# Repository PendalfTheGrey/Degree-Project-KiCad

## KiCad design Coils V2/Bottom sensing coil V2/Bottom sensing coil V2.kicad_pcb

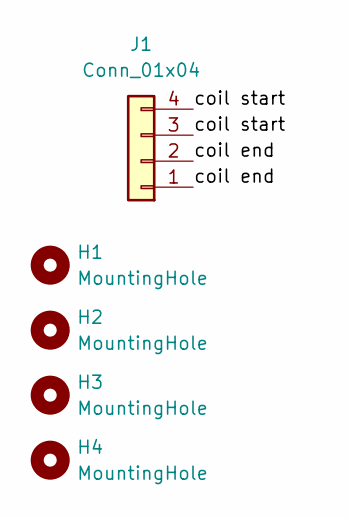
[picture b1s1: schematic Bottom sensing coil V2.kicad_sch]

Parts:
H1, H2, H3, H4: MountingHole; MountingHole_3.2mm_M3_Pad
J1: Conn_01x04; PinHeader_1x04_P2.54mm_Horizontal

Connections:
/coil end: J1.1, J1.2
/coil start: J1.3, J1.4

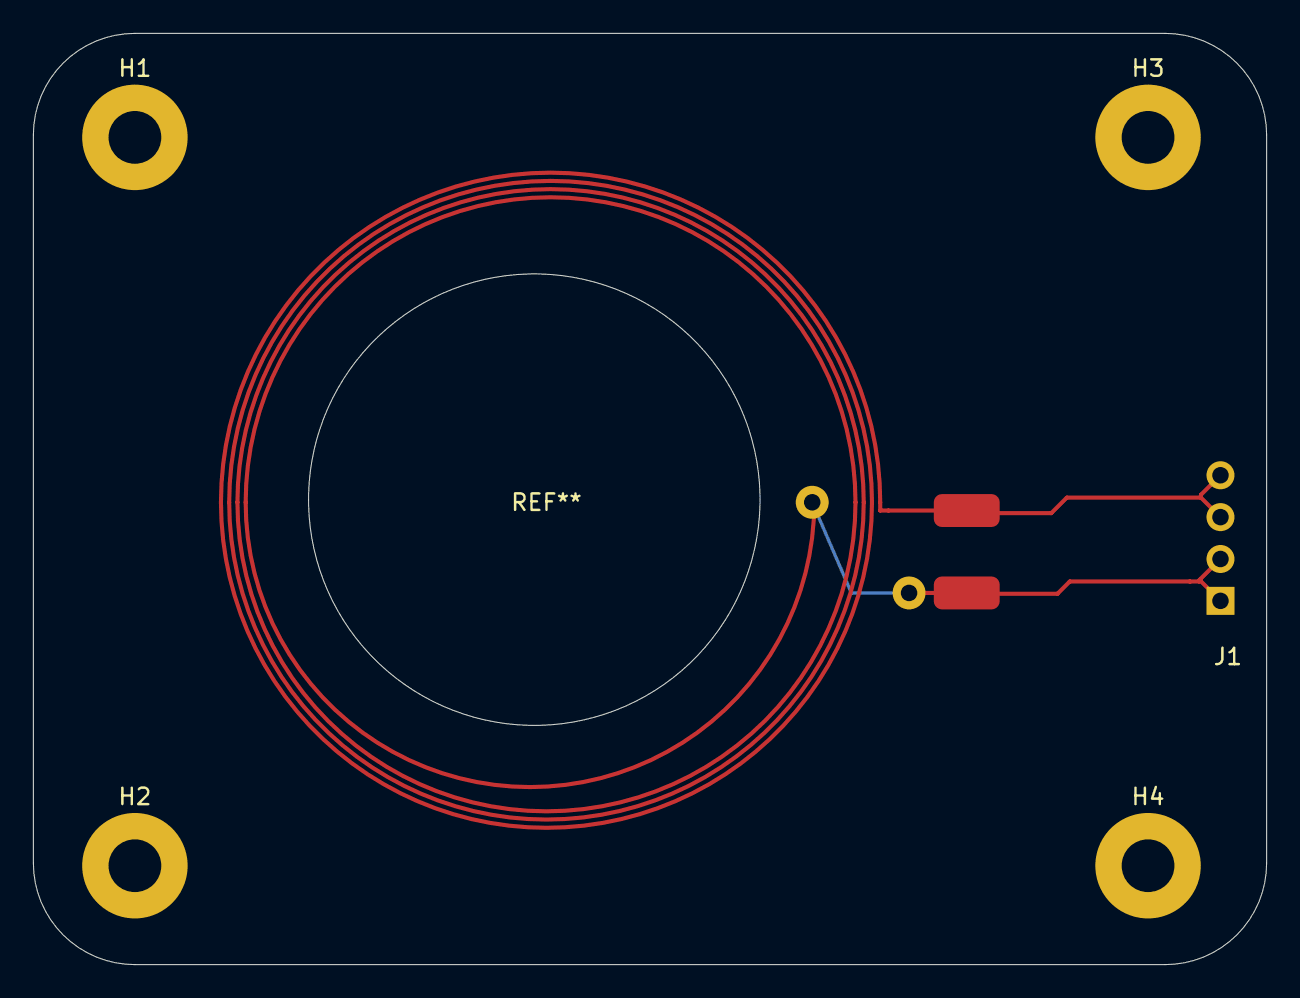
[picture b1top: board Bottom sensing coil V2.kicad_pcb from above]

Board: 2 copper layers, 74.8 x 56.5 mm, 5 parts (1 on the bottom side), 2 nets.

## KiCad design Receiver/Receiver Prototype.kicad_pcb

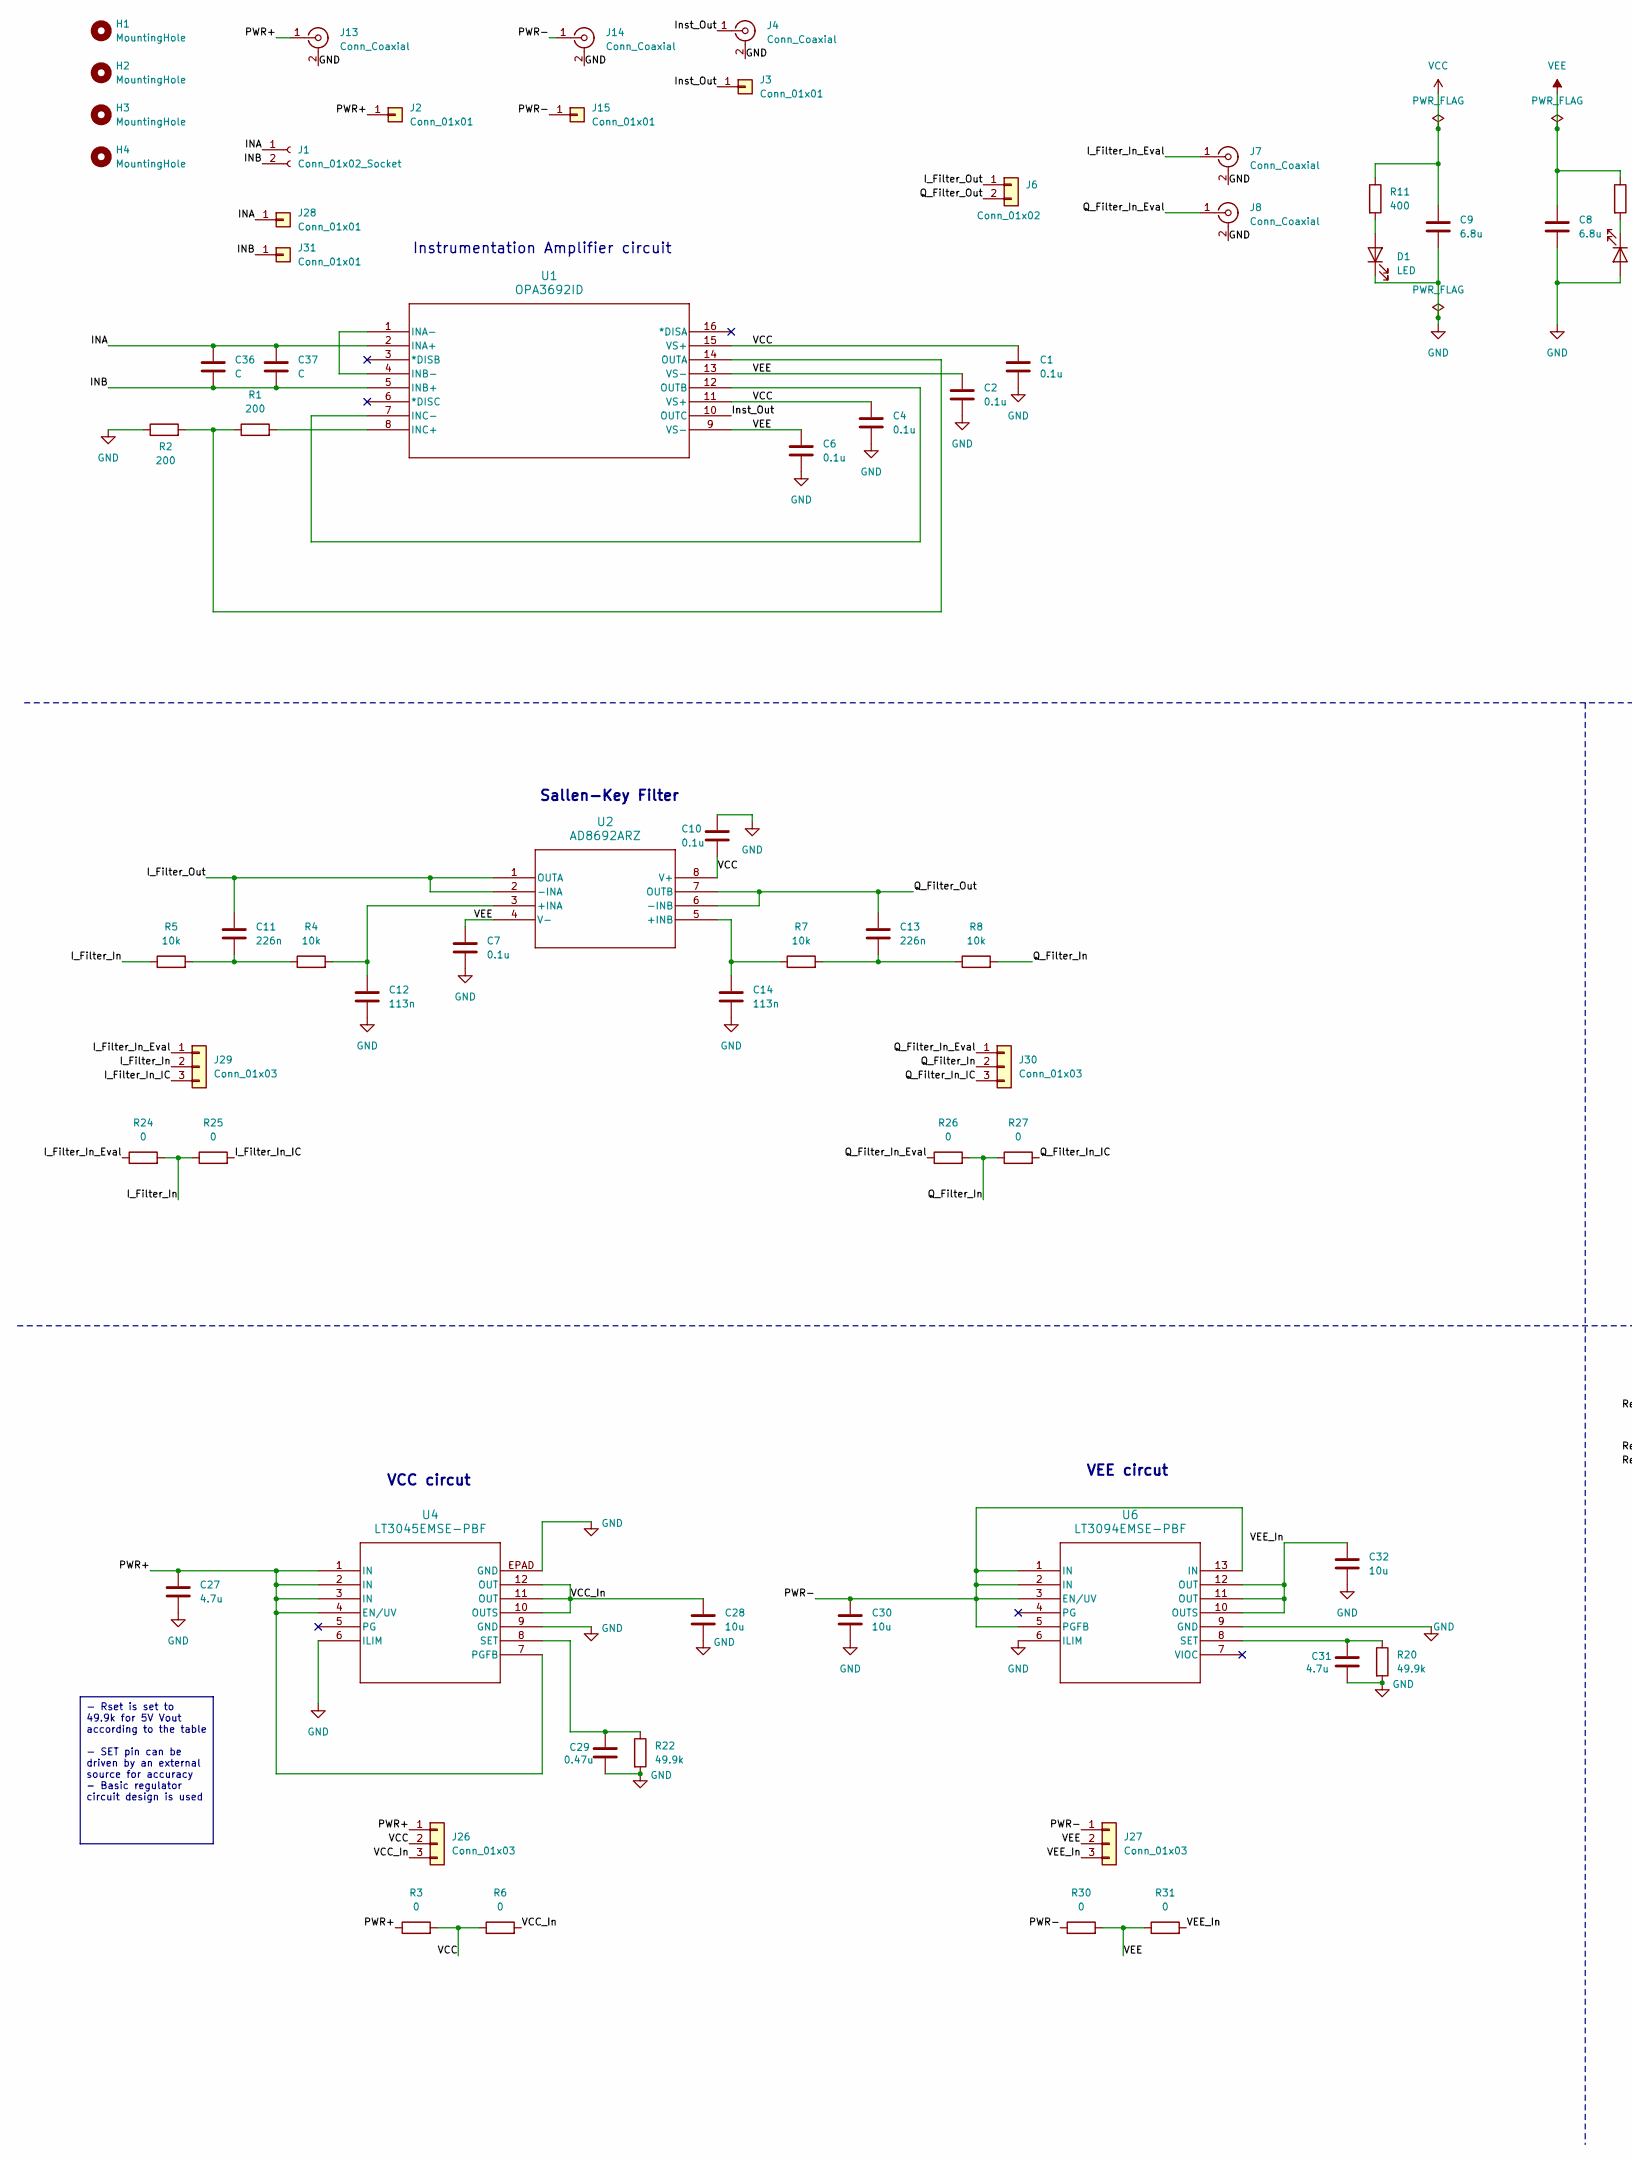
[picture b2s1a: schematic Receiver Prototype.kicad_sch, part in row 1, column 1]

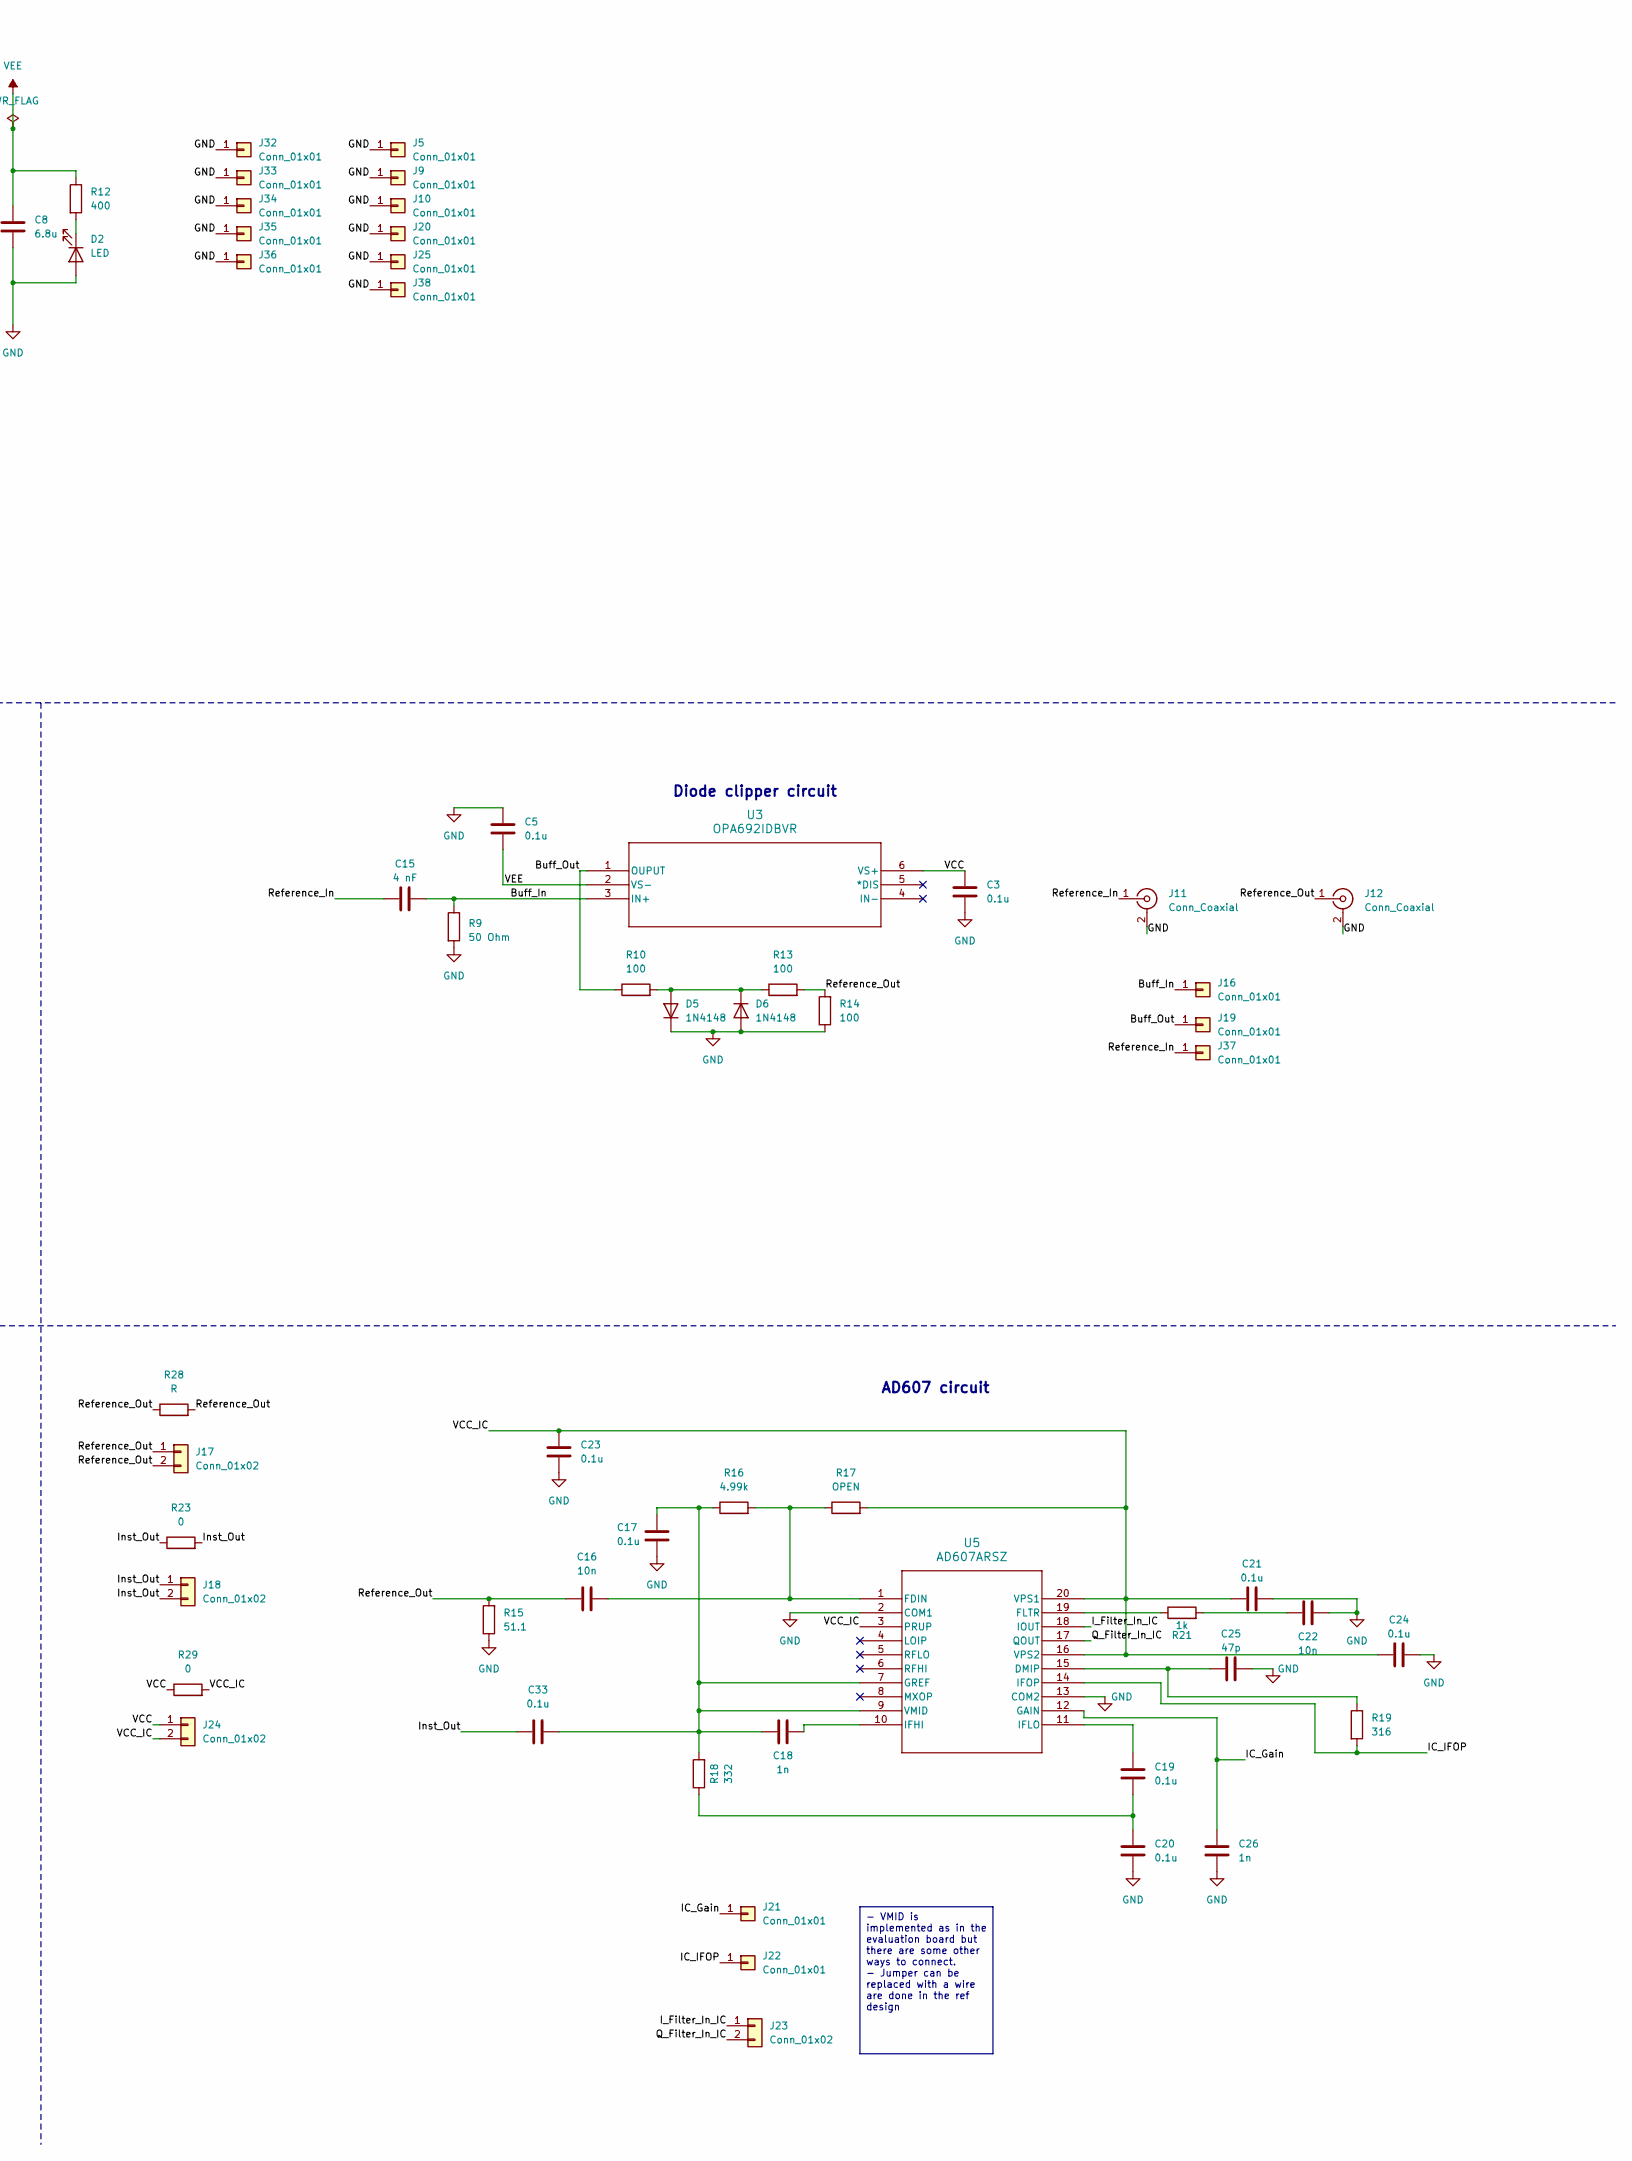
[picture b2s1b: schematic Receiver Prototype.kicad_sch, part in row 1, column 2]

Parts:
C1, C2, C3, C4, C5, C6, C7, C10, C17, C19, C20, C21, C23, C24, C33: 0.1u; C_0603_1608Metric_Pad1.08x0.95mm_HandSolder
C8, C9: 6.8u; C_0603_1608Metric_Pad1.08x0.95mm_HandSolder
C11, C13: 226n; C_0603_1608Metric_Pad1.08x0.95mm_HandSolder
C12, C14: 113n; C_0603_1608Metric_Pad1.08x0.95mm_HandSolder
C15: 4 nF; C_0603_1608Metric_Pad1.08x0.95mm_HandSolder
C16, C22: 10n; C_0603_1608Metric_Pad1.08x0.95mm_HandSolder
C18, C26: 1n; C_0603_1608Metric_Pad1.08x0.95mm_HandSolder
C25: 47p; C_0603_1608Metric_Pad1.08x0.95mm_HandSolder
C27, C31: 4.7u; C_0603_1608Metric_Pad1.08x0.95mm_HandSolder
C28, C30, C32: 10u; C_0603_1608Metric_Pad1.08x0.95mm_HandSolder
C29: 0.47u; C_0603_1608Metric_Pad1.08x0.95mm_HandSolder
C36, C37: C; C_0603_1608Metric_Pad1.08x0.95mm_HandSolder
D1, D2: LED; LED_0603_1608Metric_Pad1.05x0.95mm_HandSolder
D5, D6: 1N4148; D_0805_2012Metric_Pad1.15x1.40mm_HandSolder
H1, H2, H3, H4: MountingHole; MountingHole_3.2mm_M3_Pad
J1: Conn_01x02_Socket; PinSocket_1x02_P2.54mm_Horizontal
J2, J3, J5, J9, J10, J15, J16, J19, J20, J21, J22, J25, J28, J31, J32, J33, J34, J35, J36, J37, J38: Conn_01x01; PinHeader_1x01_P2.54mm_Vertical
J4, J7, J8, J11, J12: Conn_Coaxial; SMA_Amphenol_132289_EdgeMount
J6, J17, J18, J23, J24: Conn_01x02; PinHeader_1x02_P2.54mm_Vertical
J13, J14: Conn_Coaxial; BNC_Amphenol_112640_Edge_mount
J26, J27, J29, J30: Conn_01x03; PinHeader_1x03_P2.54mm_Vertical
R1, R2: 200; R_0603_1608Metric_Pad0.98x0.95mm_HandSolder
R3, R6, R23, R24, R25, R26, R27, R29, R30, R31: 0; R_0603_1608Metric_Pad0.98x0.95mm_HandSolder
R4, R5, R7, R8: 10k; R_0603_1608Metric_Pad0.98x0.95mm_HandSolder
R9: 50 Ohm; R_0603_1608Metric_Pad0.98x0.95mm_HandSolder
R10, R13, R14: 100; R_0603_1608Metric_Pad0.98x0.95mm_HandSolder
R11, R12: 400; R_0603_1608Metric_Pad0.98x0.95mm_HandSolder
R15: 51.1; R_0603_1608Metric_Pad0.98x0.95mm_HandSolder
R16: 4.99k; R_0603_1608Metric_Pad0.98x0.95mm_HandSolder
R17: OPEN; R_0603_1608Metric_Pad0.98x0.95mm_HandSolder
R18: 332; R_0603_1608Metric_Pad0.98x0.95mm_HandSolder
R19: 316; R_0603_1608Metric_Pad0.98x0.95mm_HandSolder
R20, R22: 49.9k; R_0603_1608Metric_Pad0.98x0.95mm_HandSolder
R21: 1k; R_0603_1608Metric_Pad0.98x0.95mm_HandSolder
R28: R; R_0603_1608Metric_Pad0.98x0.95mm_HandSolder
U1: OPA3692ID; DBQ16
U2: AD8692ARZ; SOIC127P600X175-8N
U3: OPA692IDBVR; DBV6
U4: LT3045EMSE-PBF; MSOP12_MSE_ADI
U5: AD607ARSZ; RS_20_ADI
U6: LT3094EMSE-PBF; 05-08-1666_ADI

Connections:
/Buff_In: C15.2, J16.1, R9.1, U3.3 (IN+)
/Buff_Out: J19.1, R10.1, U3.1 (OUPUT)
/IC_Gain: C26.1, J21.1, U5.12 (GAIN)
/IC_IFOP: J22.1, R19.2, U5.14 (IFOP)
/INA: C36.1, C37.1, J1.1, J28.1, U1.2 (INA+)
/INB: C36.2, C37.2, J1.2, J31.1, U1.5 (INB+)
/I_Filter_In: J29.2, R5.1, R24.2, R25.1
/I_Filter_In_Eval: J7.1 (In), J29.1, R24.1
/I_Filter_In_IC: J23.1, J29.3, R25.2, U5.18 (IOUT)
/I_Filter_Out: C11.1, J6.1, U2.1 (OUTA), U2.2 (-INA)
/Inst_Out: C33.1, J3.1, J4.1 (In), J18.1, J18.2, R23.1, R23.2, U1.10 (OUTC)
/PWR+: C27.1, J2.1, J13.1 (In), J26.1, R3.1, U4.1 (IN), U4.2 (IN), U4.3 (IN), U4.4 (EN/UV), U4.7 (PGFB)
/PWR-: C30.1, J14.1 (In), J15.1, J27.1, R30.1, U6.1 (IN), U6.2 (IN), U6.3 (EN/UV), U6.5 (PGFB), U6.13 (IN)
/Q_Filter_In: J30.2, R8.2, R26.2, R27.1
/Q_Filter_In_Eval: J8.1 (In), J30.1, R26.1
/Q_Filter_In_IC: J23.2, J30.3, R27.2, U5.17 (QOUT)
/Q_Filter_Out: C13.1, J6.2, U2.6 (-INB), U2.7 (OUTB)
/Reference_In: C15.1, J11.1 (In), J37.1
/Reference_Out: C16.1, J12.1 (In), J17.1, J17.2, R13.2, R14.2, R15.2, R28.1, R28.2
/VCC_IC: C21.1, C23.2, C24.1, J24.2, R17.2, R29.2, U5.3 (PRUP), U5.16 (VPS2), U5.20 (VPS1)
/VCC_In: C28.1, J26.3, R6.2, U4.10 (OUTS), U4.11 (OUT), U4.12 (OUT)
/VEE_In: C32.1, J27.3, R31.2, U6.10 (OUTS), U6.11 (OUT), U6.12 (OUT)
GND: C1.2, C2.2, C3.2, C4.2, C5.1, C6.2, C7.2, C8.2, C9.2, C10.1, C12.2, C14.2, C17.1, C20.2, C21.2, C22.2, C23.1, C24.2, C25.2, C26.2, C27.2, C28.2, C29.2, C30.2, C31.2, C32.2, D1.1 (K), D2.2 (A), D5.1 (K), D6.2 (A), J4.2 (Ext), J5.1, J7.2 (Ext), J8.2 (Ext), J9.1, J10.1, J11.2 (Ext), J12.2 (Ext), J13.2 (Ext), J14.2 (Ext), J20.1, J25.1, J32.1, J33.1, J34.1, J35.1, J36.1, J38.1, R2.1, R9.2, R14.1, R15.1, R20.2, R22.2, U4.6 (ILIM), U4.9 (GND), U4.EPAD (GND), U5.2 (COM1), U5.13 (COM2), U6.6 (ILIM), U6.9 (GND)
unnamed: C11.2, R4.1, R5.2
unnamed: C13.2, R7.2, R8.1
unnamed: C19.2, C20.1, R18.1
unnamed: C22.1, R21.2
unnamed: D1.2 (A), R11.2
unnamed: D2.1 (K), R12.2
unnamed: D5.2 (A), D6.1 (K), R10.2, R13.1
unnamed: U1.1 (INA-), U1.4 (INB-)
unnamed: R1.2, U1.8 (INC+)
unnamed: U1.7 (INC-), U1.12 (OUTB)
unnamed: R1.1, R2.2, U1.14 (OUTA)
unnamed: C12.1, R4.2, U2.3 (+INA)
unnamed: C14.1, R7.1, U2.5 (+INB)
unnamed: C29.1, R22.1, U4.8 (SET)
unnamed: C25.1, R19.1, U5.15 (DMIP)
unnamed: C16.2, R16.2, R17.1, U5.1 (FDIN)
unnamed: R21.1, U5.19 (FLTR)
unnamed: C17.2, C18.1, C33.2, R16.1, R18.2, U5.7 (GREF), U5.9 (VMID)
unnamed: C18.2, U5.10 (IFHI)
unnamed: C19.1, U5.11 (IFLO)
unnamed: C31.1, R20.1, U6.8 (SET)
VCC: C1.1, C3.1, C4.1, C9.1, C10.2, J24.1, J26.2, R3.2, R6.1, R11.1, R29.1, U1.11 (VS+), U1.15 (VS+), U2.8 (V+), U3.6 (VS+)
VEE: C2.1, C5.2, C6.1, C7.1, C8.1, J27.2, R12.1, R30.2, R31.1, U1.9 (VS-), U1.13 (VS-), U2.4 (V-), U3.2 (VS-)

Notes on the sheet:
- Rset is set to 49.9k for 5V Vout according to the table - SET pin can be driven by an external source for accuracy - Basic regulator circuit design is used
- VMID is implemented as in the evaluation board but there are some other ways to connect. - Jumper can be replaced with a wire are done in the ref design
AD607 circuit
VCC circut
Diode clipper circuit
Instrumentation Amplifier circuit
Sallen-Key Filter
VEE circut

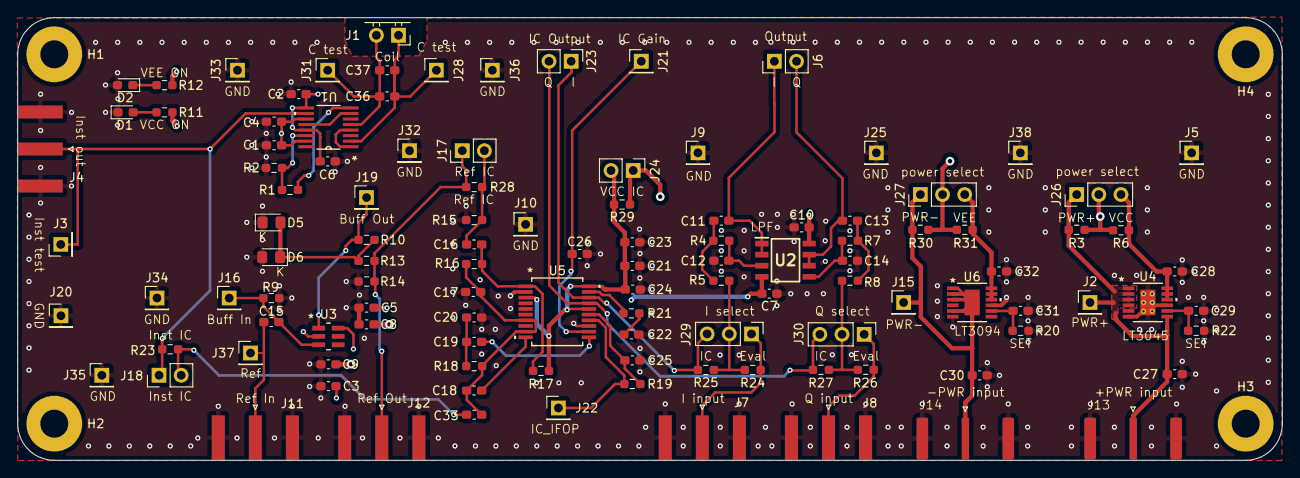
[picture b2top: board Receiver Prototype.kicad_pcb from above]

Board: 4 copper layers, 145.0 x 50.8 mm, 118 parts (0 on the bottom side), 46 nets.

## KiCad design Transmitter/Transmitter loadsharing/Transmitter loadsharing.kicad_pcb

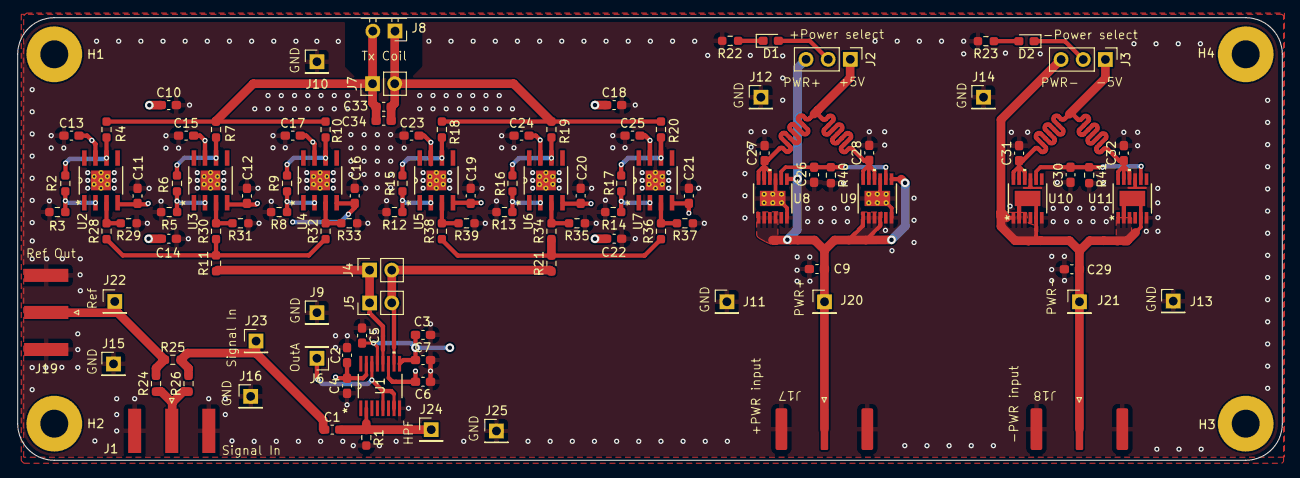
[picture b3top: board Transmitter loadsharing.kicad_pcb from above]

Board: 4 copper layers, 145.0 x 50.8 mm, 115 parts (0 on the bottom side), 40 nets.

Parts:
C1: 4 nF; C_0603_1608Metric_Pad1.08x0.95mm_HandSolder
C2, C3, C10, C14, C18, C22: 6.8uF; C_0603_1608Metric_Pad1.08x0.95mm_HandSolder
C4, C5, C6, C7, C11, C12, C13, C15, C16, C17, C19, C20, C21, C23, C24, C25: 0.1uF; C_0603_1608Metric_Pad1.08x0.95mm_HandSolder
C9, C27, C28, C31, C32: 10uF; C_0603_1608Metric_Pad1.08x0.95mm_HandSolder
C26: 0.47uF; C_0603_1608Metric_Pad1.08x0.95mm_HandSolder
C29: 22uF; C_0603_1608Metric_Pad1.08x0.95mm_HandSolder
C30: 4.7uF; C_0603_1608Metric_Pad1.08x0.95mm_HandSolder
C33, C34: C; C_0603_1608Metric_Pad1.08x0.95mm_HandSolder
D1, D2: LED; LED_0603_1608Metric_Pad1.05x0.95mm_HandSolder
H1, H2, H3, H4: MountingHole; MountingHole_3.2mm_M3_Pad
J1, J19: Conn_Coaxial; SMA_Amphenol_132289_EdgeMount
J2, J3: Conn_01x03; PinHeader_1x03_P2.54mm_Vertical
J4: Conn_01x02_Socket; PinSocket_1x02_P2.54mm_Vertical
J5, J7: Conn_01x02; PinHeader_1x02_P2.54mm_Vertical
J6, J9, J10, J11, J12, J13, J14, J15, J16, J20, J21, J22, J23, J24, J25: Conn_01x01; PinHeader_1x01_P2.54mm_Vertical
J8: Conn_01x02_Socket Horizontal; PinSocket_1x02_P2.54mm_Horizontal
J17, J18: Conn_Coaxial; BNC_Amphenol_112640_Edge_mount
R1, R24, R25, R26: 50Ω; R_0603_1608Metric_Pad0.98x0.95mm_HandSolder
R2, R6, R9, R15, R16, R17: Rf; R_0603_1608Metric_Pad0.98x0.95mm_HandSolder
R3, R5, R8, R12, R13, R14: Rg; R_0603_1608Metric_Pad0.98x0.95mm_HandSolder
R4, R7, R10, R18, R19, R20: Ro; R_0603_1608Metric_Pad0.98x0.95mm_HandSolder
R11, R21: 1Ω; R_0603_1608Metric_Pad0.98x0.95mm_HandSolder
R22, R23: Rled; R_0603_1608Metric_Pad0.98x0.95mm_HandSolder
R28, R30, R32, R34, R36, R38: 0Ω; R_0603_1608Metric_Pad0.98x0.95mm_HandSolder
R29, R31, R33, R35, R37, R39: Rt; R_0603_1608Metric_Pad0.98x0.95mm_HandSolder
R40, R41: 24.9k; R_0603_1608Metric_Pad0.98x0.95mm_HandSolder
U1: OPA3692IDBQR; DBQ16
U2, U3, U4, U5, U6, U7: THS3091D; DDA8_2P28X2P28
U8, U9: LT3045EMSE-PBF; MSOP12_MSE_ADI
U10, U11: LT3094EMSE-PBF; 05-08-1666_ADI

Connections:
+5V: C2.2, C4.2, C6.2, C10.1, C13.2, C15.2, C17.2, C18.1, C23.2, C24.2, C25.2, D1.2 (A), J2.2, U1.11 (VS+), U1.15 (VS+), U2.7 (VS+), U3.7 (VS+), U4.7 (VS+), U5.7 (VS+), U6.7 (VS+), U7.7 (VS+)
-5V: C3.2, C5.2, C7.2, C11.1, C12.1, C14.1, C16.1, C19.1, C20.1, C21.1, C22.1, D2.1 (K), J3.2, U1.9 (VS-), U1.13 (VS-), U2.4 (VS-), U3.4 (VS-), U4.4 (VS-), U5.4 (VS-), U6.4 (VS-), U7.4 (VS-)
/+5V_In: C27.1, C28.1, J2.1, U8.10 (OUTS), U8.11 (OUT), U8.12 (OUT), U9.10 (OUTS), U9.11 (OUT), U9.12 (OUT)
/-5V_In: C31.1, C32.1, J3.1, U10.10 (OUTS), U10.11 (OUT), U10.12 (OUT), U11.10 (OUTS), U11.11 (OUT), U11.12 (OUT)
/PWR+: C9.1, J2.3, J17.1 (In), J20.1, U8.1 (IN), U8.2 (IN), U8.3 (IN), U8.4 (EN/UV), U8.7 (PGFB), U9.1 (IN), U9.2 (IN), U9.3 (IN), U9.4 (EN/UV), U9.7 (PGFB)
/PWR-: C29.1, J3.3, J18.1 (In), J21.1, U10.1 (IN), U10.2 (IN), U10.3 (EN/UV), U10.5 (PGFB), U10.13 (IN), U11.1 (IN), U11.2 (IN), U11.3 (EN/UV), U11.5 (PGFB), U11.13 (IN)
/Ref out: J19.1 (In), J22.1, R24.2, R25.1
/Signal in: J1.1 (In), R24.1, R26.1
/coil end: J4.2, J5.2, R21.1, U1.10 (OUTC)
/coil load end: C33.1, C34.1, J7.2, J8.1, R18.2, R19.2, R20.2
/coil load start: C33.2, C34.2, J7.1, J8.2, R4.2, R7.2, R10.2
/coil start: J4.1, J5.1, R11.1, U1.12 (OUTB)
/loadshare input +: R11.2, R28.1, R30.1, R32.1
/loadshare input -: R21.2, R34.1, R36.1, R38.1
GND: C2.1, C3.1, C4.1, C5.1, C6.1, C7.1, C9.2, C10.2, C11.2, C12.2, C13.1, C14.2, C15.1, C16.2, C17.1, C18.2, C19.2, C20.2, C21.2, C22.2, C23.1, C24.1, C25.1, C26.2, C27.2, C28.2, C29.2, C30.2, C31.2, C32.2, J1.2 (Ext), J9.1, J10.1, J11.1, J12.1, J13.1, J14.1, J15.1, J16.1, J17.2 (Ext), J18.2 (Ext), J19.2 (Ext), J25.1, R1.2, R3.1, R5.1, R8.1, R12.1, R13.1, R14.1, R22.2, R23.2, R29.1, R31.1, R33.1, R35.1, R37.1, R39.1, R40.2, R41.2, U1.8 (INC+), U2.EPAD, U3.EPAD, U4.EPAD, U5.EPAD, U6.EPAD, U7.EPAD, U8.6 (ILIM), U8.9 (GND), U8.EPAD (GND), U9.6 (ILIM), U9.9 (GND), U9.EPAD (GND), U10.6 (ILIM), U10.9 (GND), U11.6 (ILIM), U11.9 (GND)
unnamed: D1.1 (K), R22.1
unnamed: D2.2 (A), R23.1
unnamed: J6.1, U1.5 (INB+), U1.7 (INC-), U1.14 (OUTA)
unnamed: C1.1, J23.1, R25.2, R26.2
unnamed: C1.2, J24.1, R1.1, U1.2 (INA+)
unnamed: R28.2, R29.2, U2.3 (VIN+)
unnamed: R2.2, R3.2, U2.2 (VIN-)
unnamed: R2.1, R4.1, U2.6 (VOUT)
unnamed: R30.2, R31.2, U3.3 (VIN+)
unnamed: R5.2, R6.2, U3.2 (VIN-)
unnamed: R6.1, R7.1, U3.6 (VOUT)
unnamed: R32.2, R33.2, U4.3 (VIN+)
unnamed: R8.2, R9.2, U4.2 (VIN-)
unnamed: R9.1, R10.1, U4.6 (VOUT)
unnamed: R38.2, R39.2, U5.3 (VIN+)
unnamed: R12.2, R15.2, U5.2 (VIN-)
unnamed: R15.1, R18.1, U5.6 (VOUT)
unnamed: R34.2, R35.2, U6.3 (VIN+)
unnamed: R13.2, R16.2, U6.2 (VIN-)
unnamed: R16.1, R19.1, U6.6 (VOUT)
unnamed: R36.2, R37.2, U7.3 (VIN+)
unnamed: R14.2, R17.2, U7.2 (VIN-)
unnamed: R17.1, R20.1, U7.6 (VOUT)
unnamed: C26.1, R40.1, U8.8 (SET), U9.8 (SET)
unnamed: C30.1, R41.1, U10.8 (SET), U11.8 (SET)

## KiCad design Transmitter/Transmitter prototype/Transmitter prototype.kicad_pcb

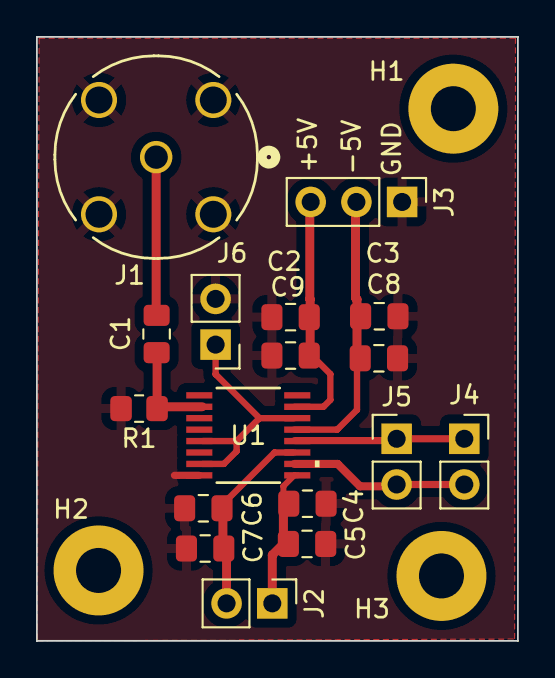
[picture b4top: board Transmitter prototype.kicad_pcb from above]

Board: 2 copper layers, 26.7 x 33.6 mm, 20 parts (0 on the bottom side), 8 nets.

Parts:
C1: 4 nF; C_0805_2012Metric_Pad1.18x1.45mm_HandSolder
C2, C3, C5, C7: 6.8 uF; C_0805_2012Metric_Pad1.18x1.45mm_HandSolder
C4, C6, C8: 0.1uF; C_0805_2012Metric_Pad1.18x1.45mm_HandSolder
C9: 0.1 uF; C_0805_2012Metric_Pad1.18x1.45mm_HandSolder
H1, H2, H3: MountingHole; MountingHole_2.5mm_Pad
J1: Conn_Coaxial; CONN_112404_AMP
J2, J5, J6: Conn_01x02; PinHeader_1x02_P2.54mm_Vertical
J3: Conn_01x03; PinHeader_1x03_P2.54mm_Vertical
J4: Conn_01x02_Socket; PinSocket_1x02_P2.54mm_Vertical
R1: 50 Ohm; R_0805_2012Metric_Pad1.20x1.40mm_HandSolder
U1: OPA3692IDBQT; DBQ16

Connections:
+5V: C2.2, C6.2, C7.1, C9.2, J2.2, J3.3, U1.11 (VS+), U1.15 (VS+)
-5V: C3.2, C4.2, C5.1, C8.2, J2.1, J3.2, U1.9 (VS-), U1.13 (VS-)
/coil end: J4.2, J5.2, U1.10 (OUTC)
/coil start: J4.1, J5.1, U1.12 (OUTB)
GND: C2.1, C3.1, C4.1, C5.2, C6.1, C7.2, C8.1, C9.1, J1.2 (Ext), J1.3, J1.4, J1.5, J3.1, J6.2, R1.2, U1.8 (INC+)
unnamed: C1.1, J1.1 (In)
unnamed: J6.1, U1.5 (INB+), U1.7 (INC-), U1.14 (OUTA)
unnamed: C1.2, R1.1, U1.2 (INA+)

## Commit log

2024-04-05 Receiver schematics without testing points added
2024-04-05 Added a folder for the project
2024-04-05 Initial transmiiter prototype push
2024-04-05 added symbol for OPA3692
2024-04-09 Changed coax footprint for TX added pinheaders for test points for out A and coil start / end
2024-04-10 added output to schematic at receiver
2024-04-10 attempted to add .gitignore
2024-04-10 Added own .gitignore file
2024-04-15 Finished receiver prototype schematic
2024-04-16 First receiver pcb layout (not connected)
2024-04-17 Receiver PCB design v1 complete. DRC passed. Component's lables not added
2024-04-17 mostly changes to transmitter prototype, for using the prototyper
2024-04-18 Added AD8692 footprint
2024-04-18 added footprints for SOIC and SSOP for OPA3692
2024-04-18 This revision includes BNC connectors, SSOP packages, minor fixes and some basic lables
2024-04-18 added 3d models for OPA3692, THS3091 and BNC connector
2024-04-18 added .gitignore to subdirectories
2024-04-19 minor fixes
2024-04-19 Added 3D models
2024-04-21 Added models for power regulators and OPA692 buffer. Also added diode clipper schematics
2024-04-22 Added AD607 to schematic
2024-04-23 Receiver schematic complete. ERC not passed due to issues with GND
2024-04-25 Receiver ready for DR2. DRC not passed due to SMA connectors
2024-04-26 First revision of Tx board
2024-04-26 Small corrections, changed footprint for edge SMA connectors
2024-04-26 Added test point after HPF and§ capactitors for coil tuning
2024-04-26 added 3d model for horizontal BNC connector
2024-04-26 version before review with Saul
2024-04-26 Added via stiching to TX board, moved almost all vias off of pads, increased the trace width for the power supply and changed coil connector to horizontal socket
2024-04-28 dkldsfjks.
2024-04-28 Moved some components. Design not complete for the DR2
2024-04-28 Receiver ready for design review 2
2024-04-29 Fixed spacing between ICs, tried to make traces the same length each of the loadsharing op-amps
2024-04-29 Receiver minor fixes before DR2
2024-04-30 Added filter input select for In-phase
2024-04-30 git being weird
2024-04-30 trying to resolve missing dir
2024-04-30 Changed symbol for THS to add EPAD connection, fixed thermal vias on footprint, fixed THS3091 dir
2024-04-30 Drew a footprint for a BNC edge connector 112640, made sure coils are centered and as symmetrical as possible:wq
2024-05-01 Added new diodes and 3d models for BNC
2024-05-01 added LTM8049 symbol/footprint
2024-05-01 added bnc 3d model
2024-05-01 added 3d model for BNC edge connector
2024-05-01 layout ocd
2024-05-02 not enough room?
2024-05-02 Final version before review 3
2024-05-02 Changed the AD8692 and SMD diodes footprints
2024-05-03 routed swithcing regulator
2024-05-03 blurp
2024-05-03 Connected COM1 to Ground in AD607
2024-05-04 Changed the Receiver layout as discussed on DR3
2024-05-05 Fixed minor changes at Receiver
2024-05-06 small changes to coils
2024-05-08 Final version sent to JLCPCB
2024-06-27 Revision 1
2024-06-27 Fixed shorting of +-5V_In and +-5V nets
2024-06-27 Fixed orientation of LED at -5V supply
2024-06-27 receiver corrected
2024-07-02 Minor fixes on receiver schematic
2024-07-02 Modified Receiver layout
2024-07-15 Receiver ready for the second revision
2024-07-16 Added an alternative version of the gradiometer
